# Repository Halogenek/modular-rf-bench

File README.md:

# Modular RF Bench

I came across an awesome system for rapid prototyping RF and Microwave solutions
by connecting individual components on small PCBs, just like LEGO.
This [Modular building block system for RF and microwave design of prototypes](https://patents.google.com/patent/US10784633B2/en?assignee=X-Microwave&oq=X-Microwave) is in my opinion a very clever way of building RF
circuits. On their [website](https://www.xmicrowave.com/) the sell almost every
available modern RF IC or passive network in a form of a rectangle PCBs.

The whole system is well polished and every part has some sort of improvement.
For example the boards interconnection has a ground cutout, probably for better
impedance matching. The connection is done (according to their patent) with a
small piece with diamond particles that improve contact. That's why they claim
that this system can be used up to ~67 GHz.

Of course this performance comes at a price.

# My own design
I liked this idea so much that I wanted to check how *bad* will standard FR4
boards perform if someone would make a system like this one. But without all
those whistles.

So I made ten different designs inspired by that system. Ordered it on PcbWay.
And when will it arrive I will test it with my VNA.

---
After some time the boards arrived in decent quality. I soldered SMA connectors
to two boards designed for them and screwed them to the PCB base, together with
a small interconnecting PCB.

I tried to follow X Microwave design but my idea had some problems. The small
board with the number 011 that was designed to connect other boards didn't make
good contact after mounted with screws. It just bulged up and the center signal
trace didn't touched the traces on the other PCBs. But after adding a small
amount of solder to the trace it started to work.

## Measurements
### Measurements of two connected SMA adapters done on nanoVNA.
*S11 50 Ohm termination*

*S11 50 Ohm termination by Port 2 of nanoVNA*

### Measurements of two connected SMA adapters done on better VNA.
*S11 50 Ohm termination*

*S11 50 Ohm termination by Port 2 of VNA*

*S21*

I wasn't excepting much after 0,8 mm FR4 PCB but it is usable up to 1,5 GHz.
The board to board connection is working and everything is pretty durable.

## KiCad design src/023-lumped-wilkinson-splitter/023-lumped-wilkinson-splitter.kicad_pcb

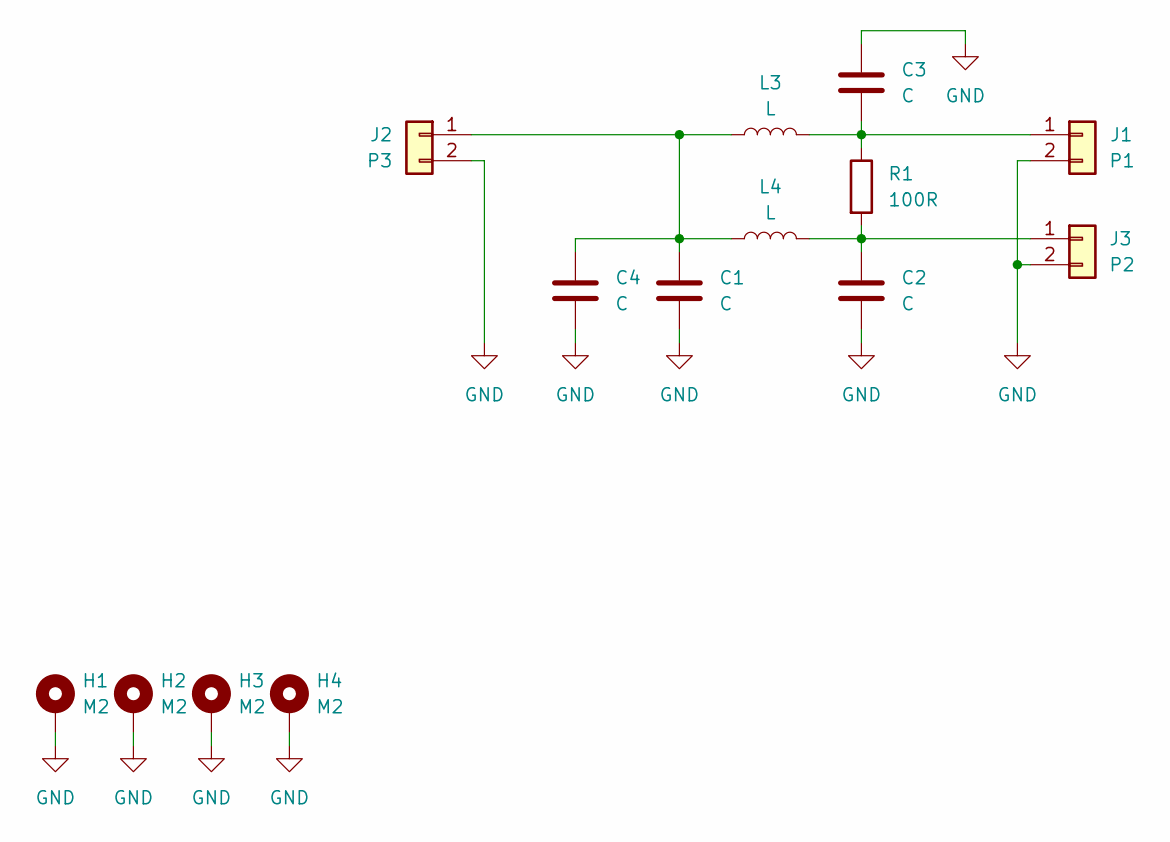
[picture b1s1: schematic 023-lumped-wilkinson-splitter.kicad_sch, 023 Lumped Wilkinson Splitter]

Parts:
C1, C2, C3, C4: C; C_0805_2012Metric
H1, H2, H3, H4: M2; M2-hole
J1: P1; edge-connector
J2: P3; edge-connector
J3: P2; edge-connector
L3, L4: L; L_0805_2012Metric
R1: 100R; R_0805_2012Metric

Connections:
GND: C1.2, C2.2, C3.1, C4.2, H1.1, H2.1, H3.1, H4.1, J1.2, J2.2, J3.2
unnamed: C3.2, J1.1, L3.2, R1.1
unnamed: C1.1, C4.1, J2.1, L3.1, L4.1
unnamed: C2.1, J3.1, L4.2, R1.2

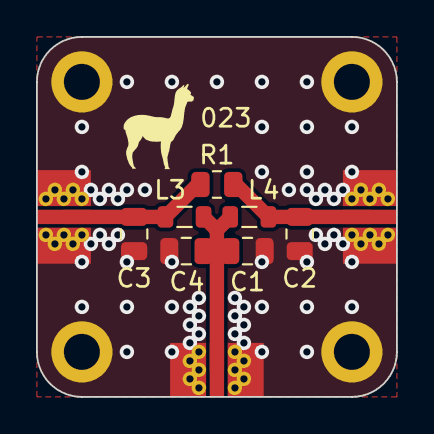
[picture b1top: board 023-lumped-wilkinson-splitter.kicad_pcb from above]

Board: 2 copper layers, 20.0 x 20.0 mm, 14 parts (0 on the bottom side), 4 nets.

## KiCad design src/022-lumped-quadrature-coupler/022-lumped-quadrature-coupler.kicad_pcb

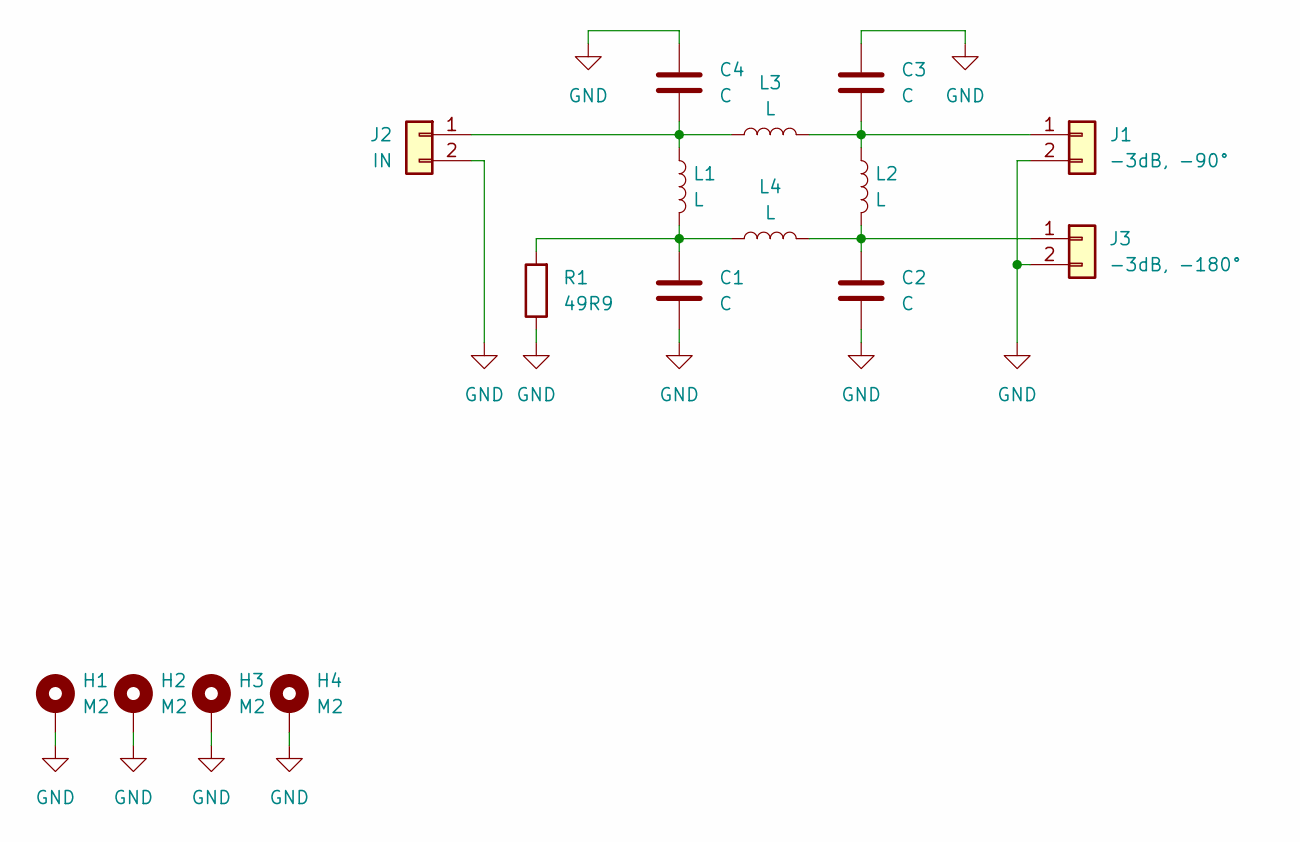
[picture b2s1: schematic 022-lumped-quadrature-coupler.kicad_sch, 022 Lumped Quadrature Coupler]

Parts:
C1, C2, C3, C4: C; C_0805_2012Metric
H1, H2, H3, H4: M2; M2-hole
J1: -3dB, -90°; edge-connector
J2: IN; edge-connector
J3: -3dB, -180°; edge-connector
L1, L2, L3, L4: L; L_0805_2012Metric
R1: 49R9; R_0805_2012Metric

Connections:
GND: C1.2, C2.2, C3.1, C4.1, H1.1, H2.1, H3.1, H4.1, J1.2, J2.2, J3.2, R1.1
unnamed: C1.1, L1.2, L4.1, R1.2
unnamed: C3.2, J1.1, L2.1, L3.2
unnamed: C4.2, J2.1, L1.1, L3.1
unnamed: C2.1, J3.1, L2.2, L4.2

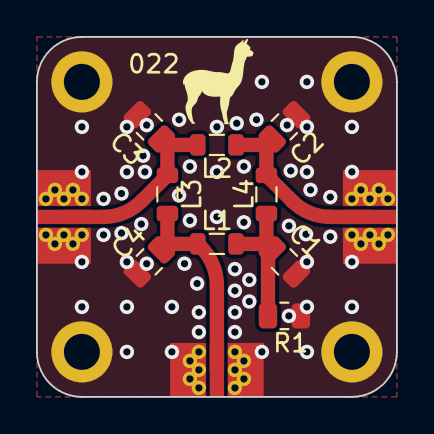
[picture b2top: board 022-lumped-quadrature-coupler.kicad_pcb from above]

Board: 2 copper layers, 20.0 x 20.0 mm, 16 parts (0 on the bottom side), 5 nets.

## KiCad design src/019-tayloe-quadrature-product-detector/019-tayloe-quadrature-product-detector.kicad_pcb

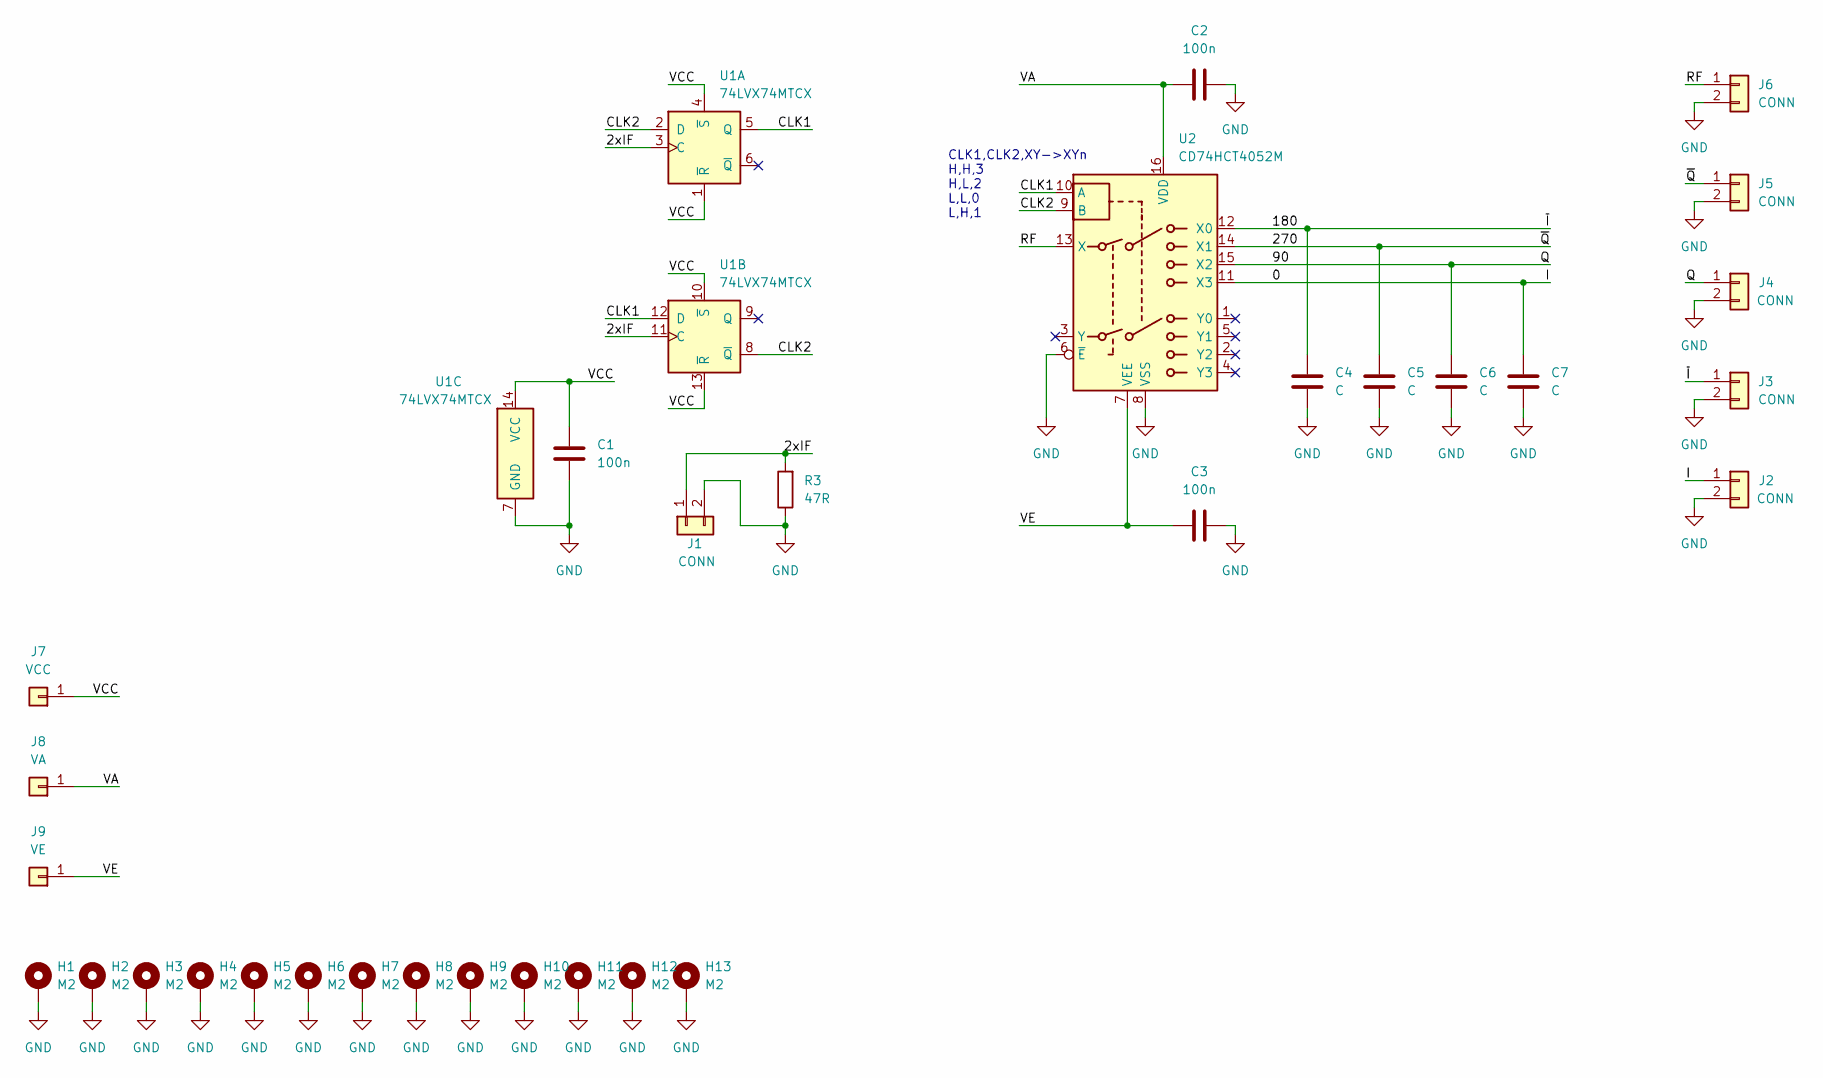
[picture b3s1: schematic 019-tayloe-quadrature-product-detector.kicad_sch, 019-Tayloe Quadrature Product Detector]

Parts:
C1, C2, C3: 100n; C_0603_1608Metric
C4, C5, C6, C7: C; C_0603_1608Metric
H1, H2, H3, H4, H5, H6, H7, H8, H9, H10, H11, H12, H13: M2; M2-hole
J1, J2, J3, J4, J5, J6: CONN; edge-connector
J7: VCC; PWR_PIN
J8: VA; PWR_PIN
J9: VE; PWR_PIN
R3: 47R; R_0603_1608Metric
U1: 74LVX74MTCX; TSSOP-14_4.4x5mm_P0.65mm
U2: CD74HCT4052M; SO-16_3.9x9.9mm_P1.27mm

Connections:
/0: C7.1, J2.1, U2.11 (X3)
/2xIF: J1.1, R3.2, U1.3 (C), U1.11 (C)
/90: C6.1, J4.1, U2.15 (X2)
/180: C4.1, J3.1, U2.12 (X0)
/270: C5.1, J5.1, U2.14 (X1)
/CLK1: U1.5 (Q), U1.12 (D), U2.10 (A)
/CLK2: U1.2 (D), U1.8 (~Q), U2.9 (B)
/RF: J6.1, U2.13 (X)
/VA: C2.1, J8.1, U2.16 (VDD)
/VCC: C1.1, J7.1, U1.1 (~R), U1.4 (~S), U1.10 (~S), U1.13 (~R), U1.14 (VCC)
/VE: C3.1, J9.1, U2.7 (VEE)
GND: C1.2, C2.2, C3.2, C4.2, C5.2, C6.2, C7.2, H1.1, H2.1, H3.1, H4.1, H5.1, H6.1, H7.1, H8.1, H9.1, H10.1, H11.1, H12.1, H13.1, J1.2, J2.2, J3.2, J4.2, J5.2, J6.2, R3.1, U1.7 (GND), U2.6 (~E), U2.8 (VSS)

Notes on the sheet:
CLK1,CLK2,XY->XYn H,H,3 H,L,2 L,L,0 L,H,1

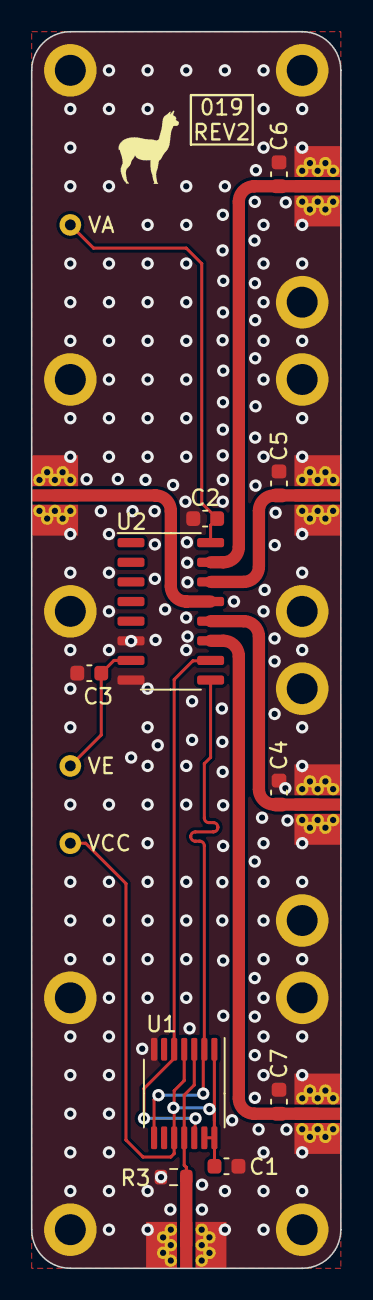
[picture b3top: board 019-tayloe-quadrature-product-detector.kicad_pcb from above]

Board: 2 copper layers, 20.0 x 80.0 mm, 32 parts (0 on the bottom side), 12 nets.

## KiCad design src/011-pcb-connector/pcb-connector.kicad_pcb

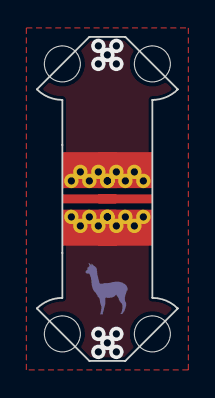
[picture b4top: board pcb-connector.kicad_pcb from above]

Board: 2 copper layers, 7.8 x 18.0 mm, 6 parts (0 on the bottom side), 2 nets, no tracks yet.

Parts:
H1, H2, H3, H4: M2; M2-hole
J1, J2: CONN; edge-connector

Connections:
GND: J1.2, J2.2
unnamed: J1.1, J2.1

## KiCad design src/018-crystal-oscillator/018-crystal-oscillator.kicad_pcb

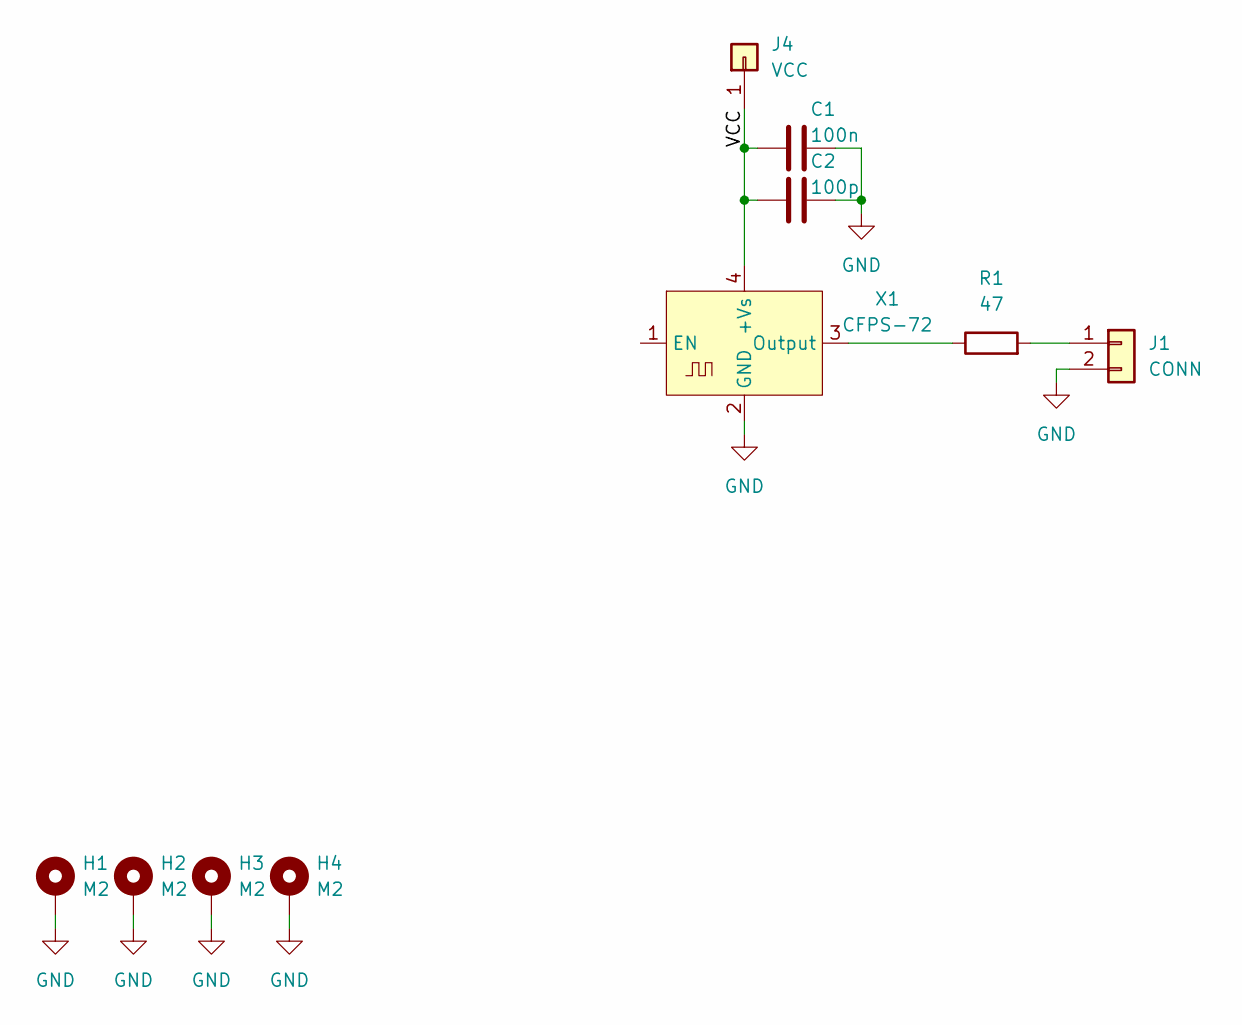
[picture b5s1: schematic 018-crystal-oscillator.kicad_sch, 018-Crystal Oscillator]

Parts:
C1: 100n; C_0603_1608Metric
C2: 100p; C_0603_1608Metric
H1, H2, H3, H4: M2; M2-hole
J1: CONN; edge-connector
J4: VCC
R1: 47; R_0603_1608Metric
X1: CFPS-72; Oscillator_SMD_IQD_IQXO70-4Pin_7.5x5.0mm

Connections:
/VCC: C1.1, C2.1, J4.1, X1.4 (+Vs)
GND: C1.2, C2.2, H1.1, H2.1, H3.1, H4.1, J1.2, X1.2 (GND)
unnamed: J1.1, R1.2
unnamed: R1.1, X1.3 (Output)

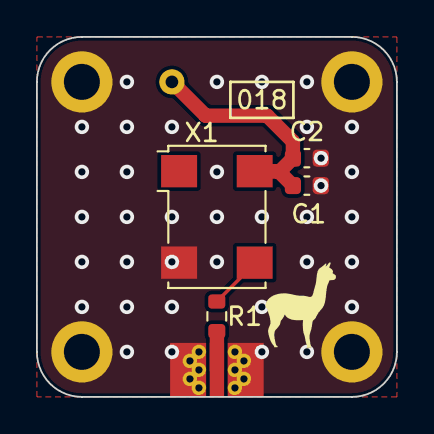
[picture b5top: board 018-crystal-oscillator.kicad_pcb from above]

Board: 2 copper layers, 20.0 x 20.0 mm, 10 parts (0 on the bottom side), 4 nets.

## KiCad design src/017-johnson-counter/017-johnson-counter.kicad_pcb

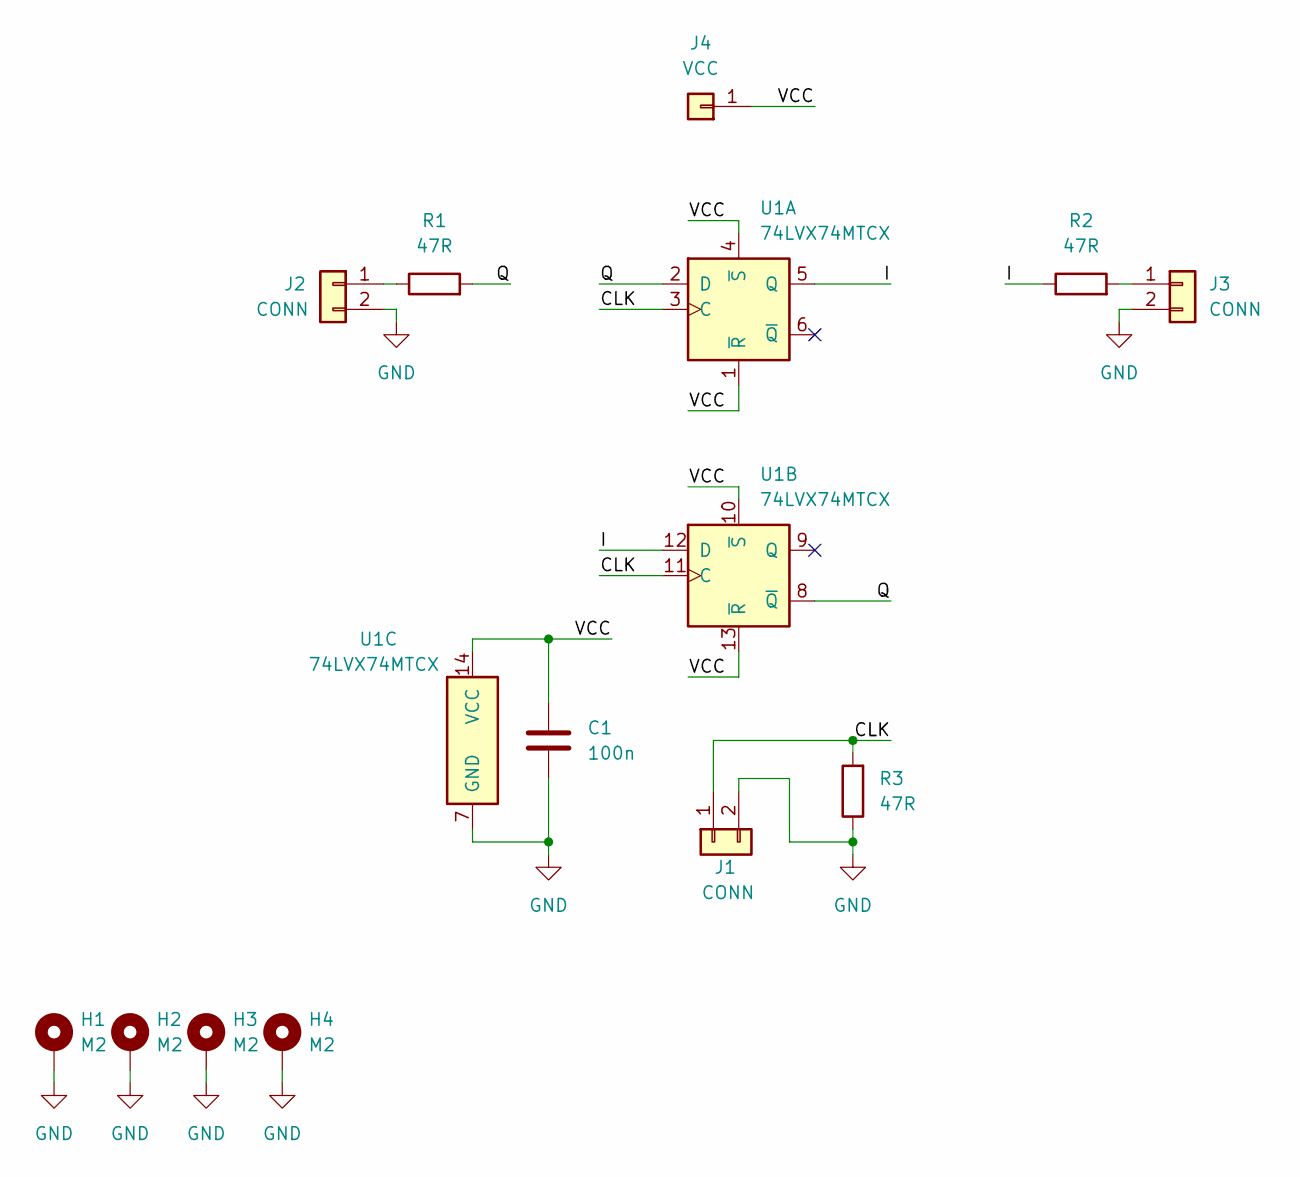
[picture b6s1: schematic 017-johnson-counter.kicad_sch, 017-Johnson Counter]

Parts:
C1: 100n; C_0603_1608Metric
H1, H2, H3, H4: M2; M2-hole
J1, J2, J3: CONN; edge-connector
J4: VCC
R1, R2, R3: 47R; R_0603_1608Metric
U1: 74LVX74MTCX; TSSOP-14_4.4x5mm_P0.65mm

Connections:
/CLK: J1.1, R3.2, U1.3 (C), U1.11 (C)
/I: R2.1, U1.5 (Q), U1.12 (D)
/Q: R1.2, U1.2 (D), U1.8 (~Q)
/VCC: C1.1, J4.1, U1.1 (~R), U1.4 (~S), U1.10 (~S), U1.13 (~R), U1.14 (VCC)
GND: C1.2, H1.1, H2.1, H3.1, H4.1, J1.2, J2.2, J3.2, R3.1, U1.7 (GND)
unnamed: J2.1, R1.1
unnamed: J3.1, R2.2

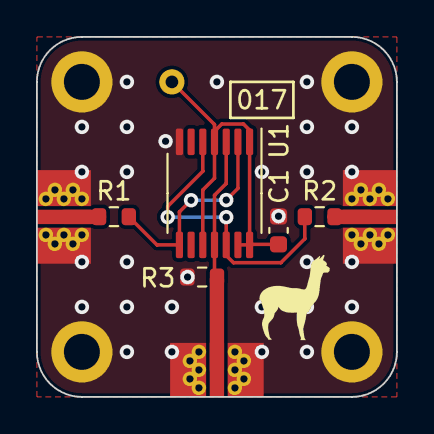
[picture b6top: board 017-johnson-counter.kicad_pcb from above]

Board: 2 copper layers, 20.0 x 20.0 mm, 13 parts (0 on the bottom side), 7 nets.

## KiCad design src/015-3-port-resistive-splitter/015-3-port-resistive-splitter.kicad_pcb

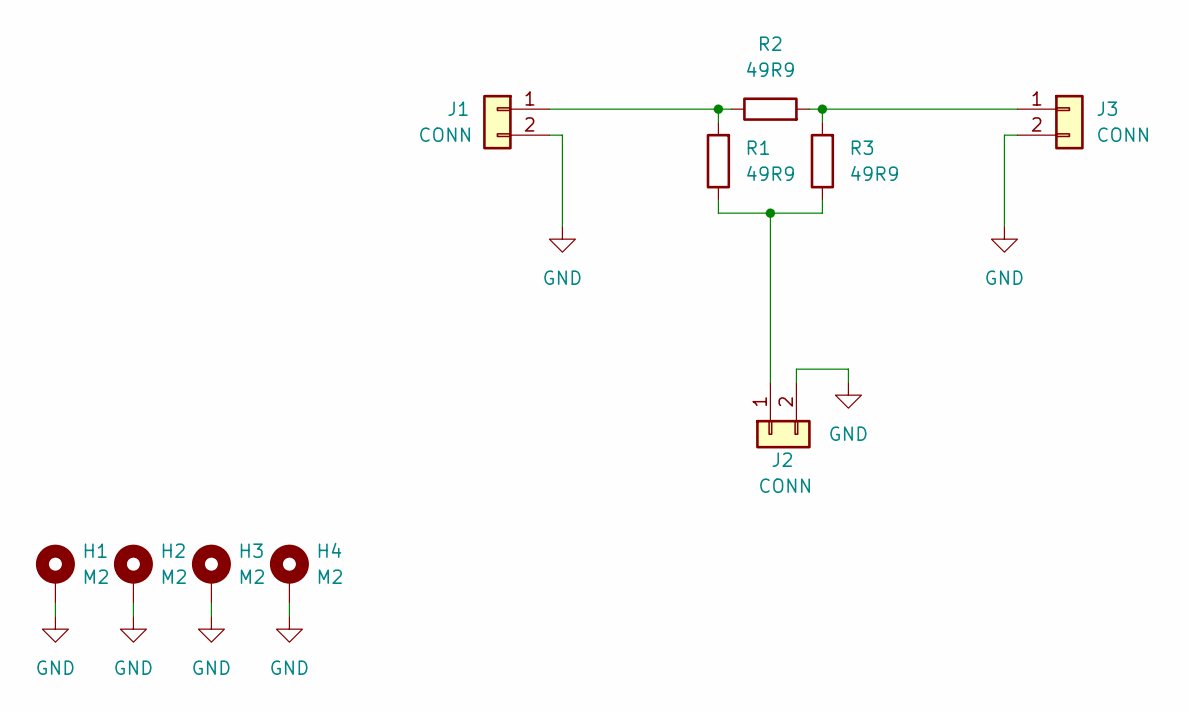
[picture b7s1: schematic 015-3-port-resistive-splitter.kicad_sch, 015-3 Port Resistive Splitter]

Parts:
H1, H2, H3, H4: M2; M2-hole
J1, J2, J3: CONN; edge-connector
R1, R2, R3: 49R9; R_0402_1005Metric

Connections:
GND: H1.1, H2.1, H3.1, H4.1, J1.2, J2.2, J3.2
unnamed: J1.1, R1.2, R2.1
unnamed: J2.1, R1.1, R3.1
unnamed: J3.1, R2.2, R3.2

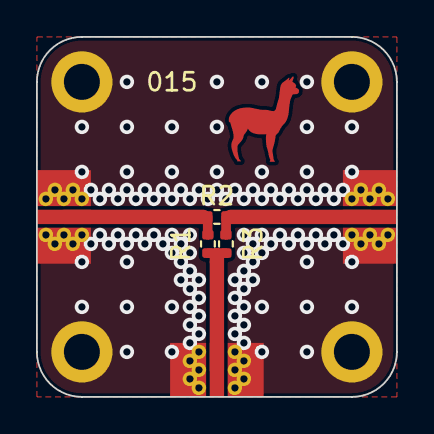
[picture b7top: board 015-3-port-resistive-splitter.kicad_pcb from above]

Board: 2 copper layers, 20.0 x 20.0 mm, 10 parts (0 on the bottom side), 4 nets.

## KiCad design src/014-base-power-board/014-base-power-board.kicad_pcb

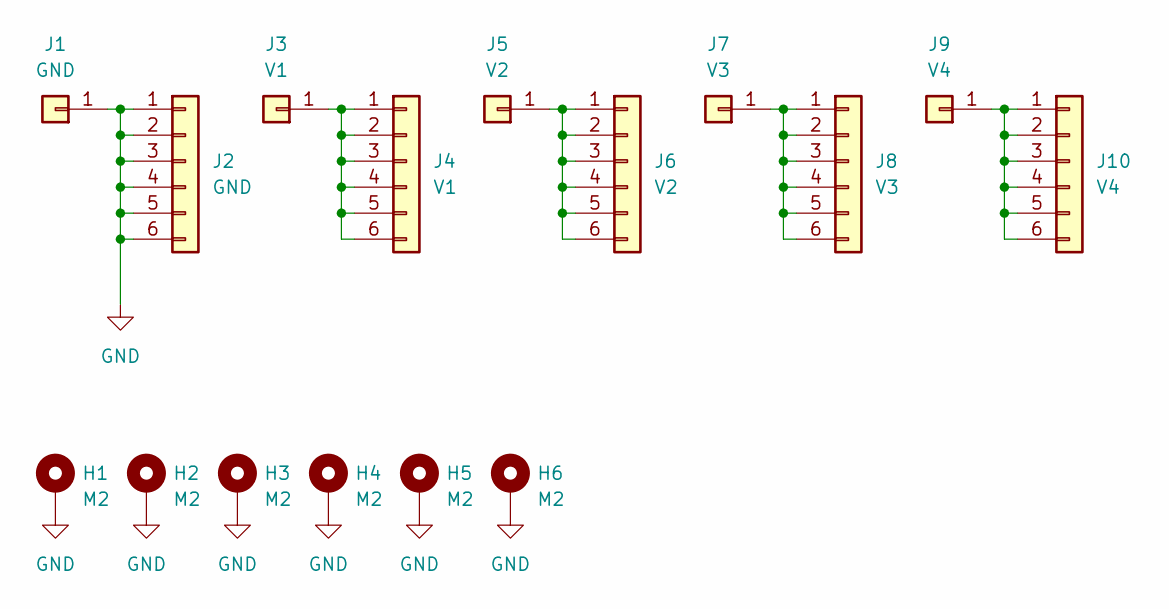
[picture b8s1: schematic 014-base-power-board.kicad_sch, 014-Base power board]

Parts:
H1, H2, H3, H4, H5, H6: M2; M2-hole
J1: GND; GC4012-F
J2: GND; PinHeader_1x06_P2.54mm_Vertical_SMD_Pin1Left
J3: V1; GC4012-F
J4: V1; PinHeader_1x06_P2.54mm_Vertical_SMD_Pin1Left
J5: V2; GC4012-F
J6: V2; PinHeader_1x06_P2.54mm_Vertical_SMD_Pin1Left
J7: V3; GC4012-F
J8: V3; PinHeader_1x06_P2.54mm_Vertical_SMD_Pin1Left
J9: V4; GC4012-F
J10: V4; PinHeader_1x06_P2.54mm_Vertical_SMD_Pin1Left

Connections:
GND: H1.1, H2.1, H3.1, H4.1, H5.1, H6.1, J1.1, J2.1, J2.2, J2.3, J2.4, J2.5, J2.6
unnamed: J3.1, J4.1, J4.2, J4.3, J4.4, J4.5, J4.6
unnamed: J5.1, J6.1, J6.2, J6.3, J6.4, J6.5, J6.6
unnamed: J7.1, J8.1, J8.2, J8.3, J8.4, J8.5, J8.6
unnamed: J9.1, J10.1, J10.2, J10.3, J10.4, J10.5, J10.6

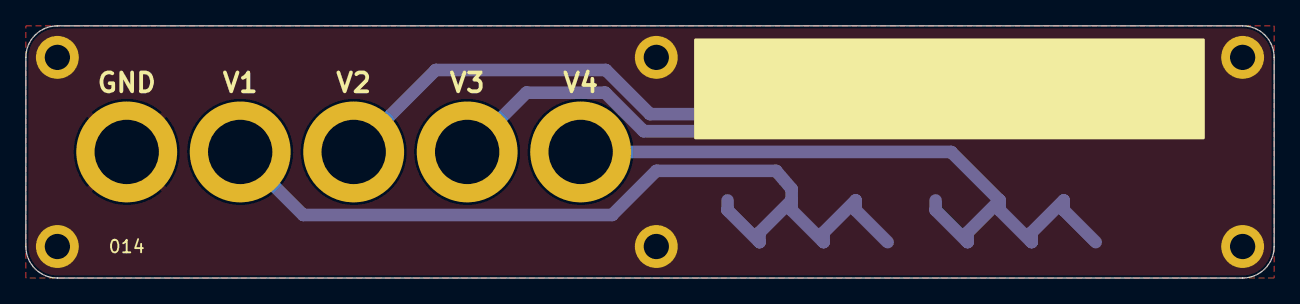
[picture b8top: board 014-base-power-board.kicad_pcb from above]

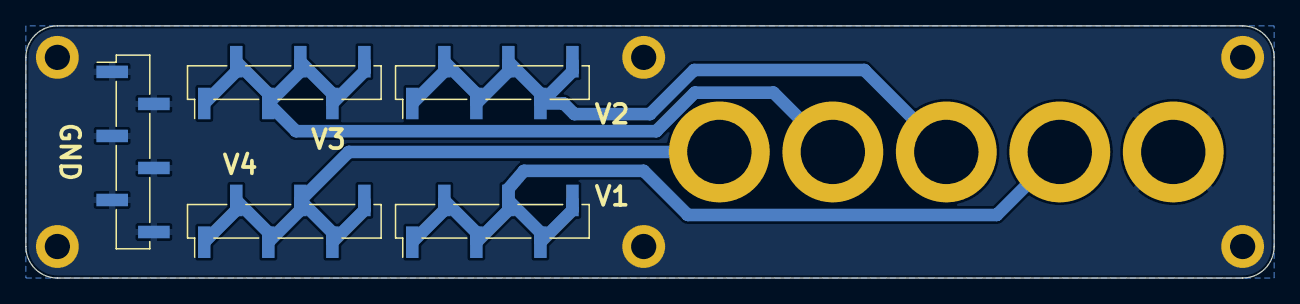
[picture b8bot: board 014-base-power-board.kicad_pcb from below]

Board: 2 copper layers, 99.0 x 20.0 mm, 16 parts (5 on the bottom side), 5 nets.

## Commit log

2022-01-22 init
2022-01-24 changing pcb connector size
2022-01-27 changing base
2022-01-27 changing sma connector pcb
2022-01-27 changing pcb connector
2022-01-27 creating 45 pcb turn connector
2022-01-28 changing pcb 45 turn
2022-01-28 starting pcb connector x2 project
2022-01-28 changing pcb connector x2 location
2022-01-29 adding filter pcb and load
2022-01-29 changing gerber layer names and fixing edge connector footprint
2022-01-30 creating balanced mixer pcb
2022-01-30 adding 009 pcb connector x3
2022-01-30 adding 010 amplifier
2022-01-31 adding different pcb connector 011
2022-02-01 fixing silkscreen in gerber files for 010
2022-03-06 fix 010-amplifier VCC pad size due short to base
2022-03-06 adding README
2022-03-06 adding CC SA licence
2022-03-13 starting script for rendering the top view of the PCBs
2022-03-13 adding scottbez's tools for generating images of the PCBs - modifications needed
2022-03-16 updating vna S11 and S21 measurements
2022-11-06 Update M2 hole size in 001 base plate
2022-11-06 Update M2 footprint. Update M2 hole size in 002.
2022-11-06 Update M2 hole size in 004. Remove 003.
2022-11-06 Remove 005.
2022-11-06 Update M2 hole size in 006.
2022-11-06 Update M2 hole size in 007.
2022-11-06 Update M2 hole size in 008.
2022-11-06 Removing 009.
2022-11-06 Update M2 hole size in 010.
2022-11-07 Update M2 hole size and type in 011.
2022-11-07 Fixing footprint library linking
2022-11-07 Creating 012 prototype board
2022-11-08 Finishing first version of python script for SVG PCB view generation
2022-11-09 Creating 013-prototype board
2022-11-10 wip/014-base-power-board
2022-11-11 Adding 014-base-power-board
2022-11-11 Fixing VCC hole size on development boards
2022-11-11 Adding 3 way power splitter
2022-11-11 Creating plastic 3D printed housing for 001-base PCB
2022-11-28 017 Johnson Counter
2022-11-28 018 crystal oscillator
2022-12-01 019-tayloe-quadrature-product-detector
2023-05-01 changing plastic base housing for a solid plate
2023-06-21 improving 3d printed base 016
2023-06-30 fixing 011-pcb-connector - too wide pcb trace and adding paste layer
2023-06-30 fixing 011-pcb-connector - adding revision on PCB
2023-07-01 adding 020 plastic base no front PCB panel
2023-07-21 Updating 019-tayloe-quadrature-product-detector for widing port spacing
2023-08-15 Adding 022 Lumped Quadrature Coupler
2023-08-19 adding 023-lumped-wilkinson-splitter
